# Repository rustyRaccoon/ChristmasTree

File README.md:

# ChristmasTree
 Small christmas tree with a bunch of LEDs and an Attiny45

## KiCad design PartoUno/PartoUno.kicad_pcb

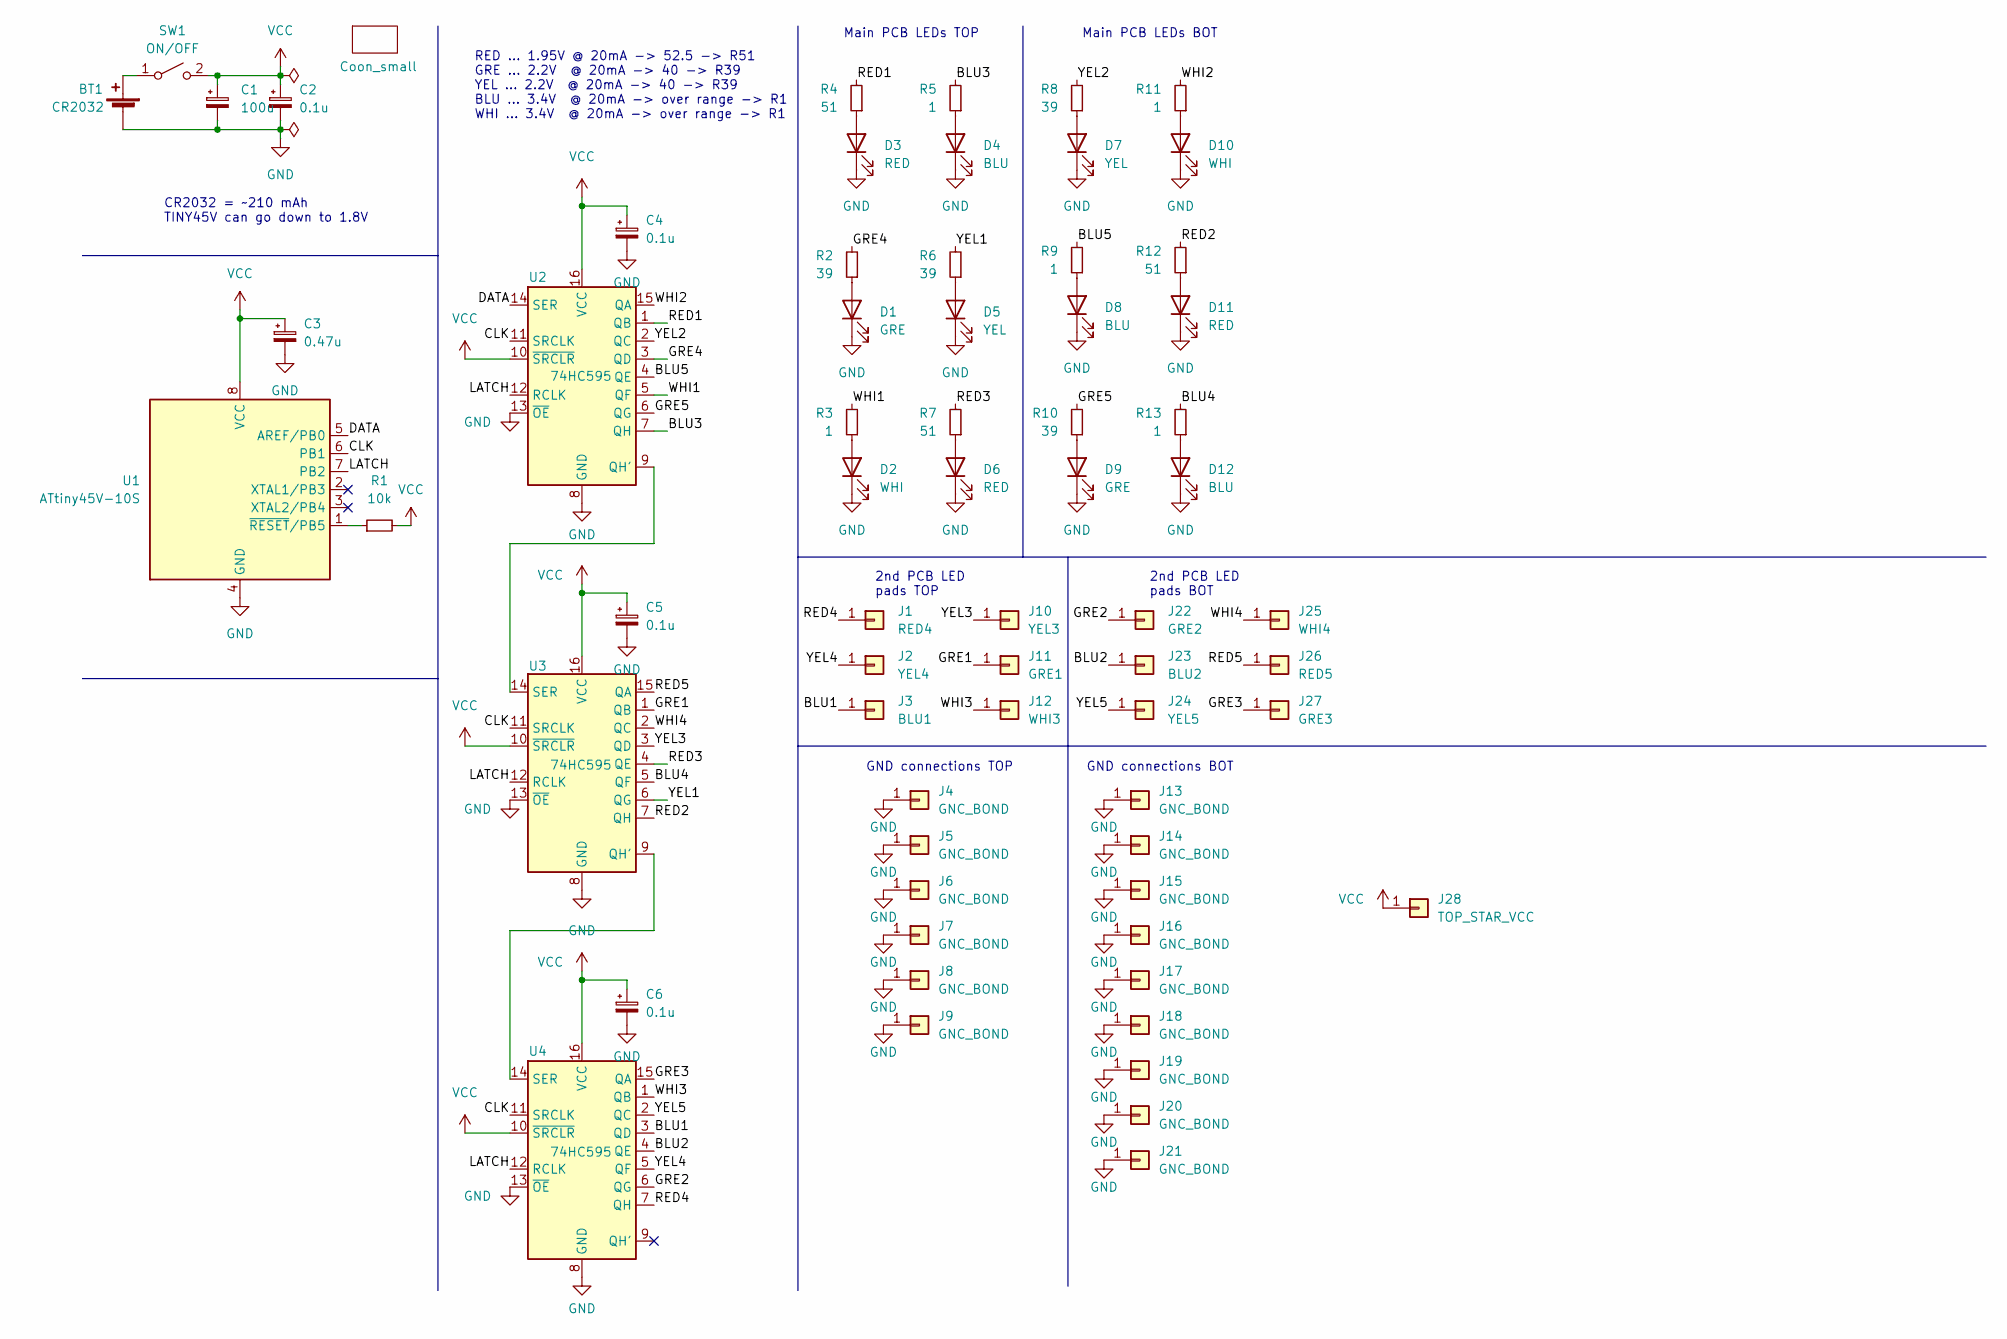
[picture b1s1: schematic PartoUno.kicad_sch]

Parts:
BT1: CR2032; 2032 battery clip; LCSC C2902340
C1: 100u; C_1210_3225Metric
C2, C4, C5, C6: 0.1u; C_1206_3216Metric
C3: 0.47u; C_1206_3216Metric
D1, D9: GRE; LED_0805_2012Metric
D2, D10: WHI; LED_0805_2012Metric
D3, D6, D11: RED; LED_0805_2012Metric
D4, D8, D12: BLU; LED_0805_2012Metric
D5, D7: YEL; LED_0805_2012Metric
J1: RED4; SolderWirePad_1x01_SMD_1x2mm
J2: YEL4; SolderWirePad_1x01_SMD_1x2mm
J3: BLU1; SolderWirePad_1x01_SMD_1x2mm
J4, J5, J6, J7, J8, J9, J13, J14, J15, J16, J17, J18, J19, J20, J21: GNC_BOND; SolderWirePad_1x01_SMD_1x2mm
J10: YEL3; SolderWirePad_1x01_SMD_1x2mm
J11: GRE1; SolderWirePad_1x01_SMD_1x2mm
J12: WHI3; SolderWirePad_1x01_SMD_1x2mm
J22: GRE2; SolderWirePad_1x01_SMD_1x2mm
J23: BLU2; SolderWirePad_1x01_SMD_1x2mm
J24: YEL5; SolderWirePad_1x01_SMD_1x2mm
J25: WHI4; SolderWirePad_1x01_SMD_1x2mm
J26: RED5; SolderWirePad_1x01_SMD_1x2mm
J27: GRE3; SolderWirePad_1x01_SMD_1x2mm
J28: TOP_STAR_VCC; SolderWirePad_1x01_SMD_1x2mm
R1: 10k; R_1206_3216Metric
R2, R6, R8, R10: 39; R_1206_3216Metric
R3, R5, R9, R11, R13: 1; R_1206_3216Metric
R4, R7, R12: 51; R_1206_3216Metric
S1: Coon_small; _Racoon_small
SW1: ON/OFF; SW_DIP_SPSTx01_Slide_6.7x4.1mm_W6.73mm_P2.54mm_LowProfile_J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
U1: ATtiny45V-10S; DIP-8_W7.62mm_Socket_LongPads
U2, U3, U4: 74HC595; TSSOP-16_4.4x5mm_P0.65mm

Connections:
/BLU1: J3.1, U4.3 (QD)
/BLU2: J23.1, U4.4 (QE)
/BLU3: R5.2, U2.7 (QH)
/BLU4: R13.2, U3.5 (QF)
/BLU5: R9.2, U2.4 (QE)
/CLK: U1.6 (PB1), U2.11 (SRCLK), U3.11 (SRCLK), U4.11 (SRCLK)
/DATA: U1.5 (AREF/PB0), U2.14 (SER)
/GRE1: J11.1, U3.1 (QB)
/GRE2: J22.1, U4.6 (QG)
/GRE3: J27.1, U4.15 (QA)
/GRE4: R2.2, U2.3 (QD)
/GRE5: R10.2, U2.6 (QG)
/LATCH: U1.7 (PB2), U2.12 (RCLK), U3.12 (RCLK), U4.12 (RCLK)
/RED1: R4.2, U2.1 (QB)
/RED2: R12.2, U3.7 (QH)
/RED3: R7.2, U3.4 (QE)
/RED4: J1.1, U4.7 (QH)
/RED5: J26.1, U3.15 (QA)
/WHI1: R3.2, U2.5 (QF)
/WHI2: R11.2, U2.15 (QA)
/WHI3: J12.1, U4.1 (QB)
/WHI4: J25.1, U3.2 (QC)
/YEL1: R6.2, U3.6 (QG)
/YEL2: R8.2, U2.2 (QC)
/YEL3: J10.1, U3.3 (QD)
/YEL4: J2.1, U4.5 (QF)
/YEL5: J24.1, U4.2 (QC)
GND: BT1.2 (-), C1.2, C2.2, C3.2, C4.2, C5.2, C6.2, D1.1 (K), D2.1 (K), D3.1 (K), D4.1 (K), D5.1 (K), D6.1 (K), D7.1 (K), D8.1 (K), D9.1 (K), D10.1 (K), D11.1 (K), D12.1 (K), J4.1, J5.1, J6.1, J7.1, J8.1, J9.1, J13.1, J14.1, J15.1, J16.1, J17.1, J18.1, J19.1, J20.1, J21.1, U1.4 (GND), U2.8 (GND), U2.13 (~OE), U3.8 (GND), U3.13 (~OE), U4.8 (GND), U4.13 (~OE)
unnamed: BT1.1 (+), SW1.1 (A)
unnamed: D1.2 (A), R2.1
unnamed: D2.2 (A), R3.1
unnamed: D3.2 (A), R4.1
unnamed: D4.2 (A), R5.1
unnamed: D5.2 (A), R6.1
unnamed: D6.2 (A), R7.1
unnamed: D7.2 (A), R8.1
unnamed: D8.2 (A), R9.1
unnamed: D9.2 (A), R10.1
unnamed: D10.2 (A), R11.1
unnamed: D11.2 (A), R12.1
unnamed: D12.2 (A), R13.1
unnamed: R1.1, U1.1 (~RESET/PB5)
unnamed: U2.9 (QH'), U3.14 (SER)
unnamed: U3.9 (QH'), U4.14 (SER)
VCC: C1.1, C2.1, C3.1, C4.1, C5.1, C6.1, J28.1, R1.2, SW1.2 (B), U1.8 (VCC), U2.10 (~SRCLR), U2.16 (VCC), U3.10 (~SRCLR), U3.16 (VCC), U4.10 (~SRCLR), U4.16 (VCC)

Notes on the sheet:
Main PCB LEDs TOP
GND connections BOT
2nd PCB LED pads BOT
GND connections TOP
RED ... 1.95V @ 20mA -> 52.5 -> R51 GRE ... 2.2V @ 20mA -> 40 -> R39 YEL ... 2.2V @ 20mA -> 40 -> R39 BLU ... 3.4V @ 20mA -> over range -> R1 WHI ... 3.4V @ 20mA -> over range -> R1
Main PCB LEDs BOT
2nd PCB LED pads TOP
CR2032 = ~210 mAh TINY45V can go down to 1.8V

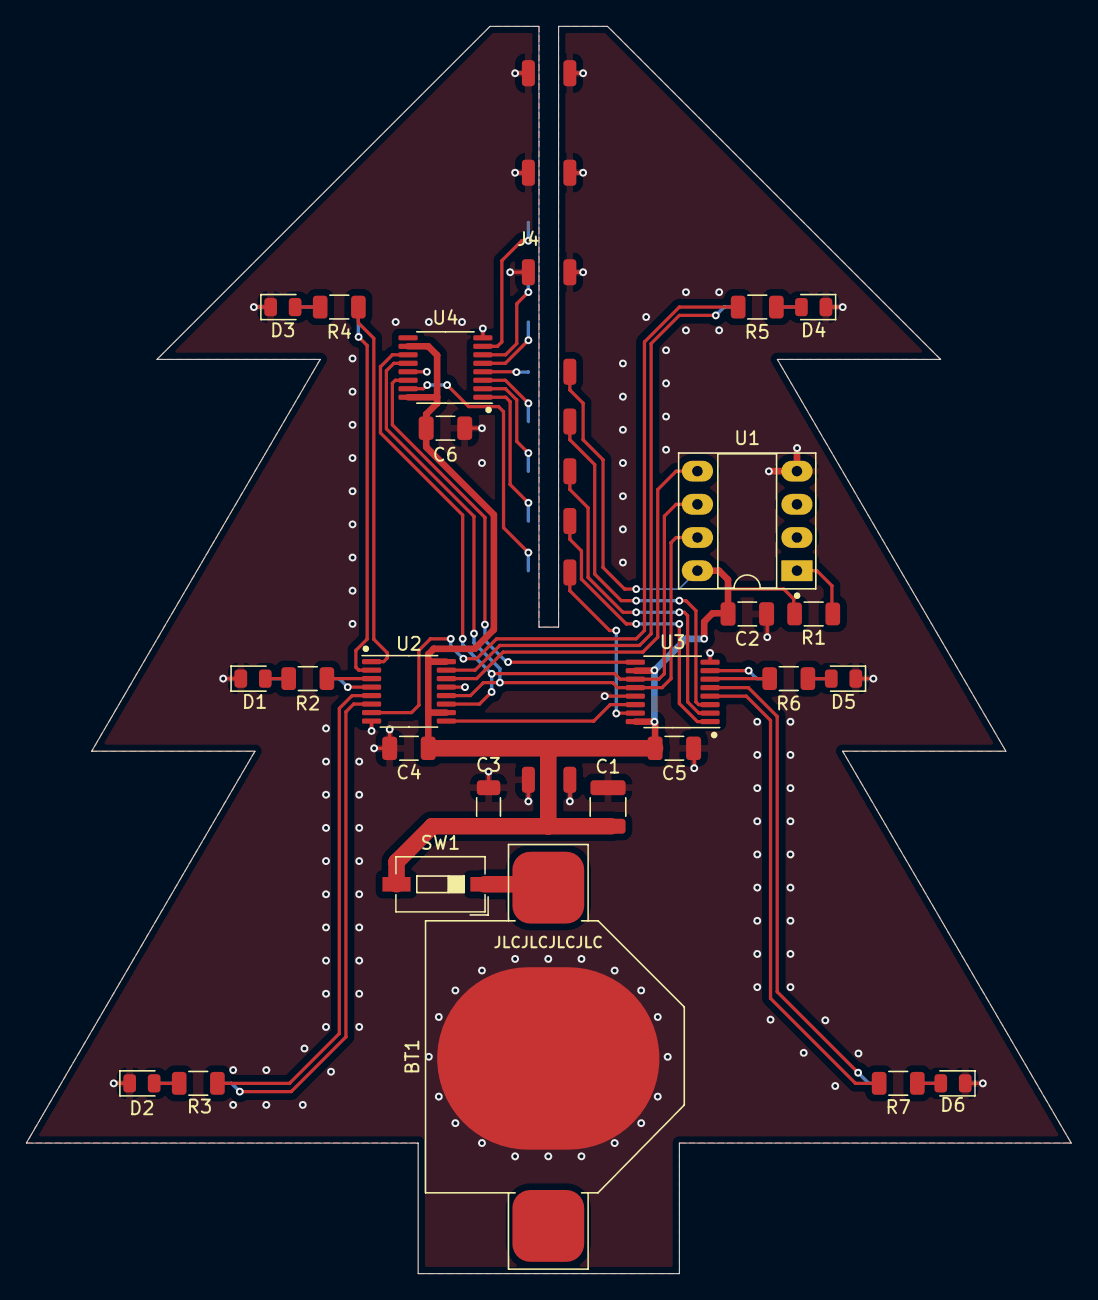
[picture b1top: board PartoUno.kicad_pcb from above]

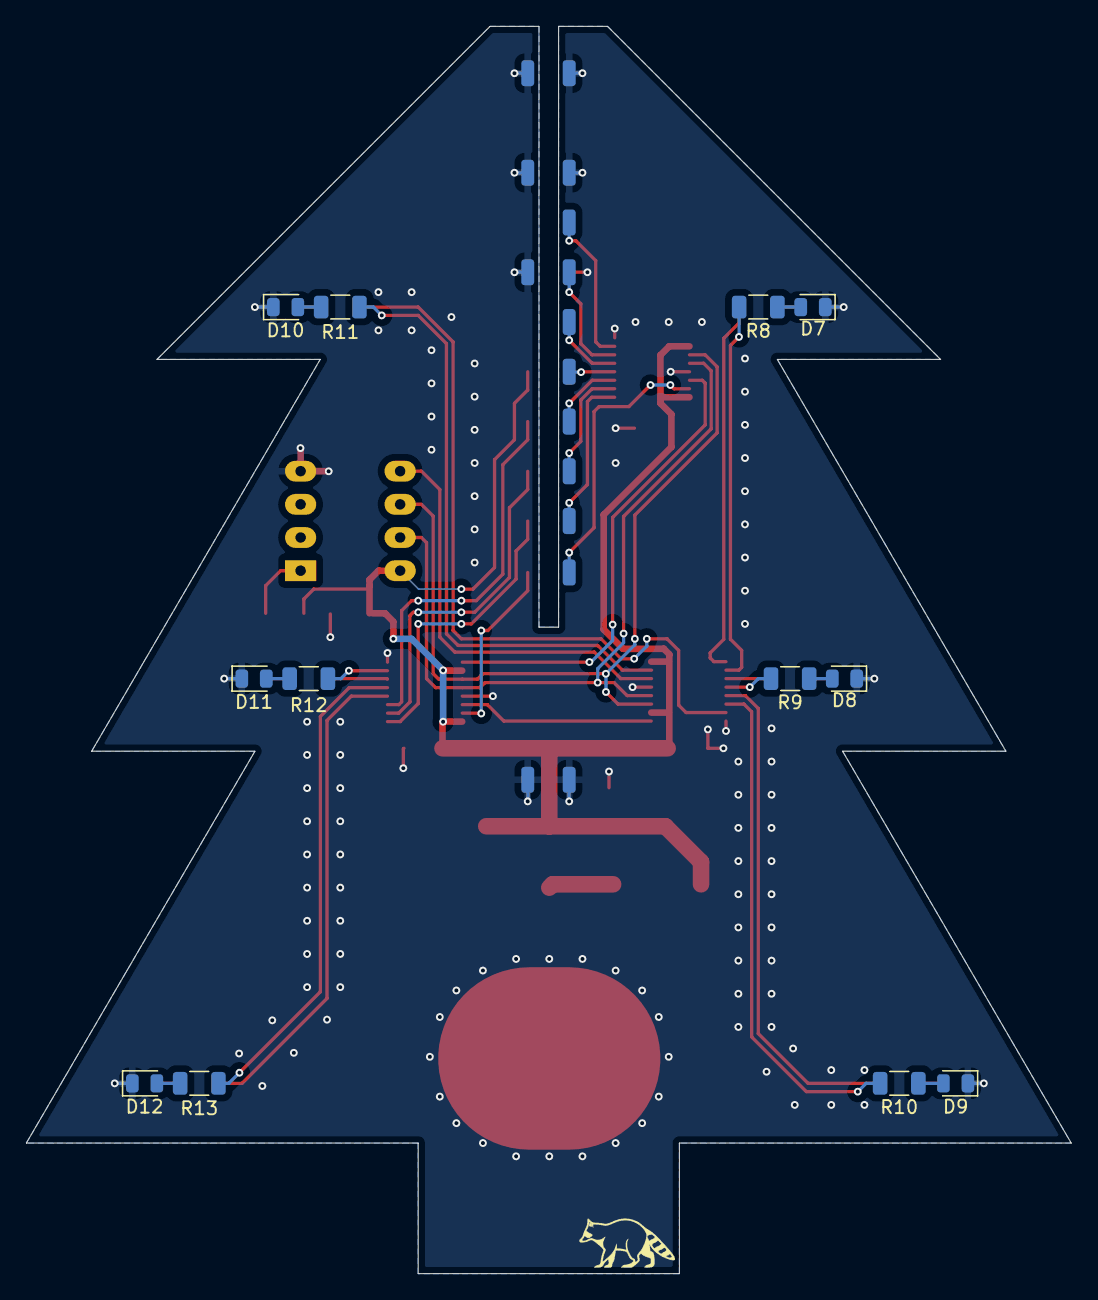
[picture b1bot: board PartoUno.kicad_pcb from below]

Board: 2 copper layers, 80.0 x 95.5 mm, 66 parts (28 on the bottom side), 45 nets.

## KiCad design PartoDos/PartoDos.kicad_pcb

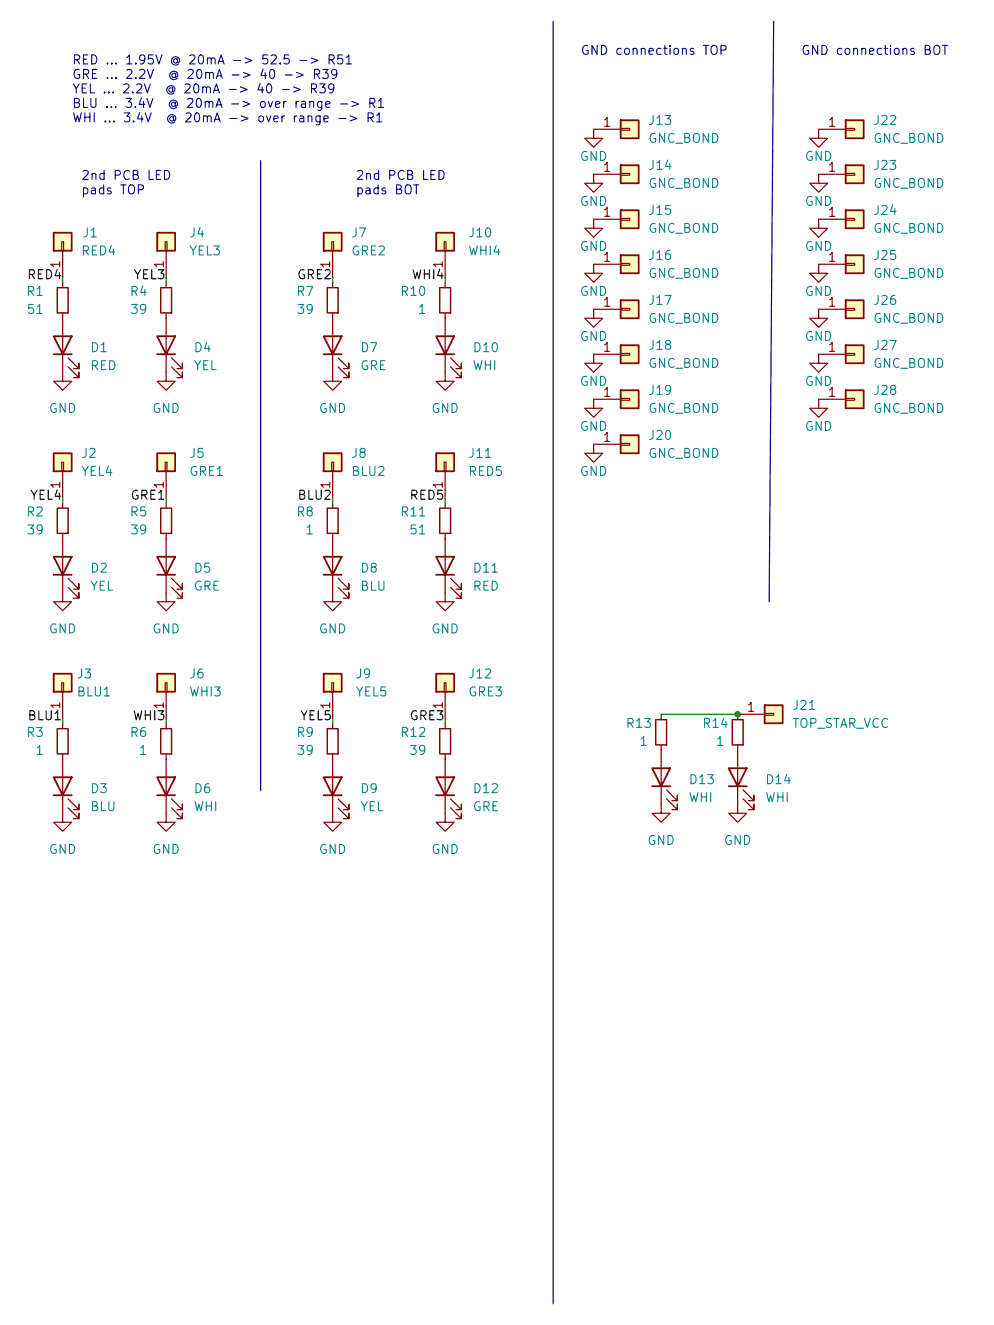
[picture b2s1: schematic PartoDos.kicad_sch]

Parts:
D1, D11: RED; LED_0805_2012Metric
D2, D4, D9: YEL; LED_0805_2012Metric
D3, D8: BLU; LED_0805_2012Metric
D5, D7, D12: GRE; LED_0805_2012Metric
D6, D10, D13, D14: WHI; LED_0805_2012Metric
J1: RED4; SolderWirePad_1x01_SMD_1x2mm
J2: YEL4; SolderWirePad_1x01_SMD_1x2mm
J3: BLU1; SolderWirePad_1x01_SMD_1x2mm
J4: YEL3; SolderWirePad_1x01_SMD_1x2mm
J5: GRE1; SolderWirePad_1x01_SMD_1x2mm
J6: WHI3; SolderWirePad_1x01_SMD_1x2mm
J7: GRE2; SolderWirePad_1x01_SMD_1x2mm
J8: BLU2; SolderWirePad_1x01_SMD_1x2mm
J9: YEL5; SolderWirePad_1x01_SMD_1x2mm
J10: WHI4; SolderWirePad_1x01_SMD_1x2mm
J11: RED5; SolderWirePad_1x01_SMD_1x2mm
J12: GRE3; SolderWirePad_1x01_SMD_1x2mm
J13, J14, J15, J16, J17, J18, J19, J20, J22, J23, J24, J25, J26, J27, J28: GNC_BOND; SolderWirePad_1x01_SMD_1x2mm
J21: TOP_STAR_VCC; SolderWirePad_1x01_SMD_1x2mm
R1, R11: 51; R_1206_3216Metric
R2, R4, R5, R7, R9, R12: 39; R_1206_3216Metric
R3, R6, R8, R10, R13, R14: 1; R_1206_3216Metric

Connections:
/BLU1: J3.1, R3.2
/BLU2: J8.1, R8.2
/GRE1: J5.1, R5.2
/GRE2: J7.1, R7.2
/GRE3: J12.1, R12.2
/RED4: J1.1, R1.2
/RED5: J11.1, R11.2
/WHI3: J6.1, R6.2
/WHI4: J10.1, R10.2
/YEL3: J4.1, R4.2
/YEL4: J2.1, R2.2
/YEL5: J9.1, R9.2
GND: D1.1 (K), D2.1 (K), D3.1 (K), D4.1 (K), D5.1 (K), D6.1 (K), D7.1 (K), D8.1 (K), D9.1 (K), D10.1 (K), D11.1 (K), D12.1 (K), D13.1 (K), D14.1 (K), J13.1, J14.1, J15.1, J16.1, J17.1, J18.1, J19.1, J20.1, J22.1, J23.1, J24.1, J25.1, J26.1, J27.1, J28.1
unnamed: D1.2 (A), R1.1
unnamed: D2.2 (A), R2.1
unnamed: D3.2 (A), R3.1
unnamed: D4.2 (A), R4.1
unnamed: D5.2 (A), R5.1
unnamed: D6.2 (A), R6.1
unnamed: D7.2 (A), R7.1
unnamed: D8.2 (A), R8.1
unnamed: D9.2 (A), R9.1
unnamed: D10.2 (A), R10.1
unnamed: D11.2 (A), R11.1
unnamed: D12.2 (A), R12.1
unnamed: D13.2 (A), R13.1
unnamed: D14.2 (A), R14.1
unnamed: J21.1, R13.2, R14.2

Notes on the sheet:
GND connections BOT
2nd PCB LED pads BOT
GND connections TOP
RED ... 1.95V @ 20mA -> 52.5 -> R51 GRE ... 2.2V @ 20mA -> 40 -> R39 YEL ... 2.2V @ 20mA -> 40 -> R39 BLU ... 3.4V @ 20mA -> over range -> R1 WHI ... 3.4V @ 20mA -> over range -> R1
2nd PCB LED pads TOP

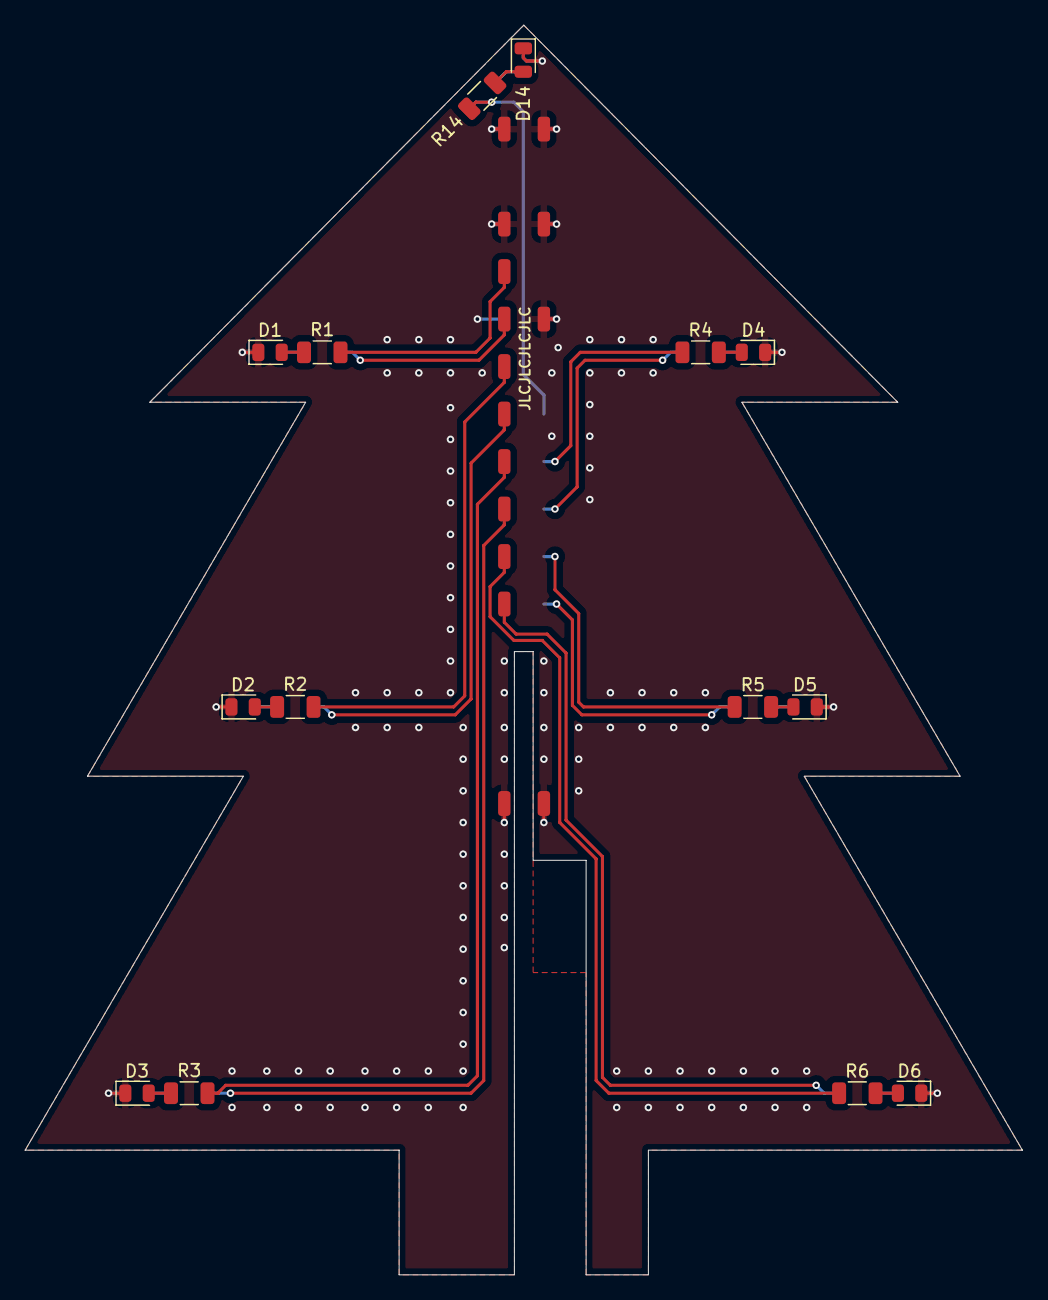
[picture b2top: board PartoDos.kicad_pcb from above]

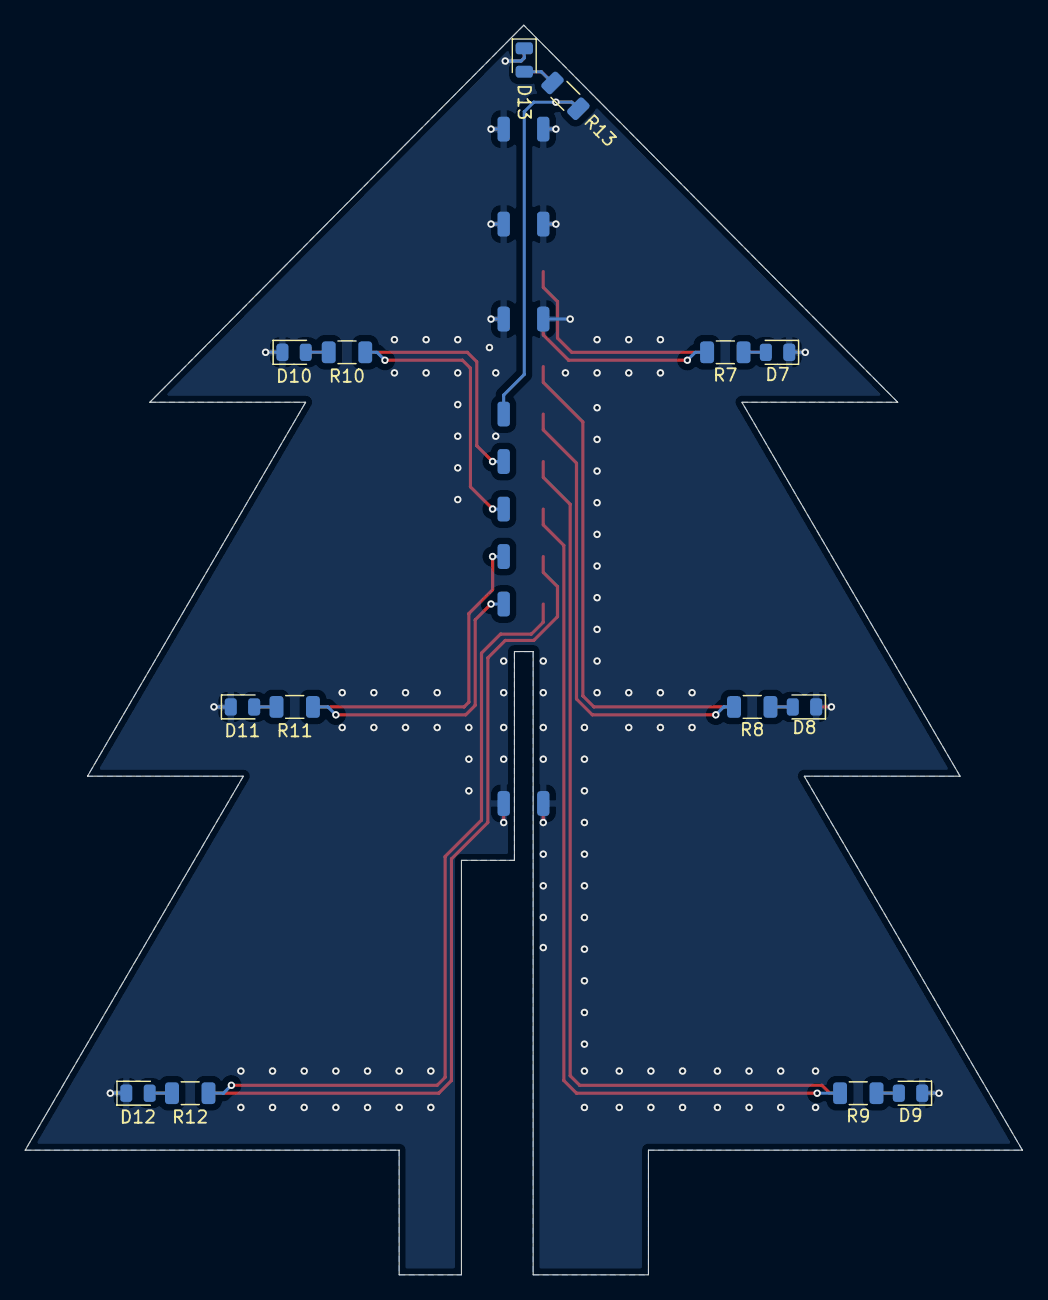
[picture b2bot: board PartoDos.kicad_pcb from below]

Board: 2 copper layers, 80.0 x 100.2 mm, 56 parts (27 on the bottom side), 28 nets.

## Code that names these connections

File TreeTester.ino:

/*
Author:	rustyRaccoon
Date:		2022-12-22
Version:	1.0
*/

/*
D12 D9 D7

Randomly cycles through all 24 LEDs on the tree.
Keeps each LED on for 700ms.
Uses https://forum.arduino.cc/t/random-option-from-array-without-repetition/484510/6
*/
// define attiny pins
#define DATA PB0
#define CLK PB1
#define LATCH PB2

// changing variables
uint32_t data;      // 32-bits for 24 LEDs
uint8_t counter;    // just to count from 0 to 23

// Prep and setup stuff goes here...
void setup() {
  cli();  // disable interrupts during setup

  pinMode(DATA, OUTPUT);   // set serial data as output
  pinMode(CLK, OUTPUT);    // set shift register clock as output
  pinMode(LATCH, OUTPUT);  // set output register (latch) clock as output

  // default conditions
  data = 0;
  counter = 0;

  sei();  // enable interrupts after setup
}

// Main loop
void loop() {
  data = 0;
  data |= (1ul << counter); 

  //Shift the data out
  digitalWrite(LATCH, 0);          // set latch pin LOW so nothing gets shifted out
  shiftOutData(DATA, CLK, data);  // shift out LED states in that layer
  digitalWrite(LATCH, 1);          // sent everything out in parallel
  
  if(counter > 23){
    counter = 0;
  }
  else{
    counter++;
  }

  delay(1000);
}

// This shifts 24 bits out MSB first, on the rising edge of the clock.
void shiftOutData(uint8_t dataPin, uint8_t clockPin, uint32_t toBeSent) {
  int i = 0;
  uint8_t pinState = 0;

  // clear everything out just in case
  digitalWrite(dataPin, 0);
  digitalWrite(clockPin, 0);

  // loop through bits in the data bytes counting DOWN in the for loop so that %00000001 or "1"
  // will go through such that it will be pin Q0 that lights.
  for (i = 23; i >= 0; i--) {
    digitalWrite(clockPin, 0);
    // if the value passed AND a bitmask result is true then set pinState to 1
    if (toBeSent & (1ul << i)) {
      pinState = 1;
    } else {
      pinState = 0;
    }

    digitalWrite(dataPin, pinState);  // sets the pin to HIGH or LOW depending on pinState
    digitalWrite(clockPin, 1);        // shifts bits on upstroke of clock pin
    digitalWrite(dataPin, 0);         // zero the data pin after shift to prevent bleed through
  }
  digitalWrite(clockPin, 0);  // stop shifting
}

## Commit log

2022-12-20 Deleted obsolete files
2022-12-22 First issue
2022-12-22 Fixed code
    Had an issue in shiftOutData where I defined the wrong data type (16 bit instead of 32 bit) so it cut all data short
2022-12-22 Added test file
2022-12-23 deleted backup files
2022-12-23 Added B.Fab layer
2022-12-24 Deleted treeTester
2022-12-30 Updated design
    + top LED
    + power switch
    ~ routing
    ~ via stitching more aligned
